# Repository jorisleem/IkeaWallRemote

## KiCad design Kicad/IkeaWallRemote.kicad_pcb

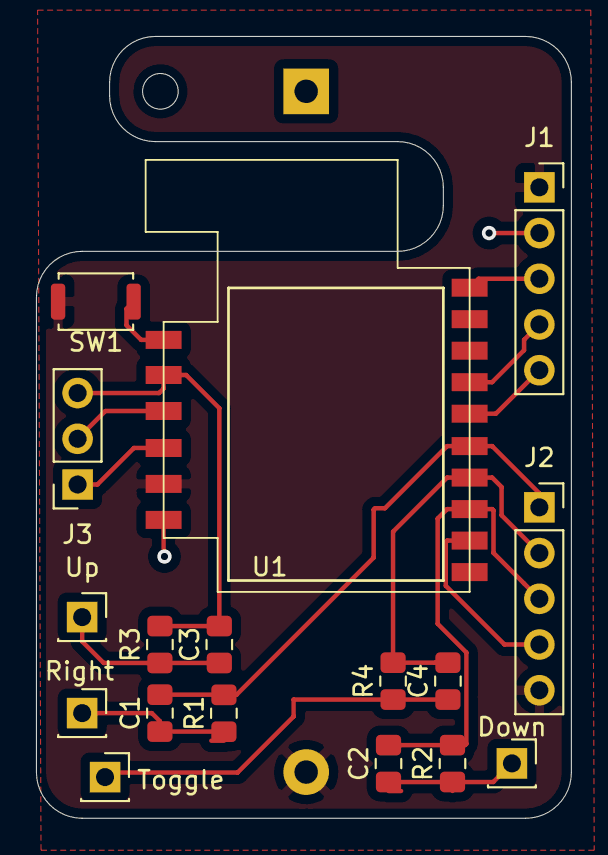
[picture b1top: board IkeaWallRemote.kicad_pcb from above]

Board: 2 copper layers, 29.7 x 43.4 mm, 18 parts (1 on the bottom side), 17 nets.

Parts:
BT1: Battery_Cell; CR123a
C1, C2, C3, C4: 10nf; C_0805_2012Metric_Pad1.15x1.40mm_HandSolder
Down: Conn_01x01_Male; PinSocket_1x01_P2.54mm_Vertical
J1, J2: Conn_01x05_Male; PinSocket_1x05_P2.54mm_Vertical
J3: Conn_01x03_Male; PinSocket_1x03_P2.54mm_Vertical
R1, R2, R3, R4: 487; R_0805_2012Metric_Pad1.15x1.40mm_HandSolder
Right: Conn_01x01_Male; PinSocket_1x01_P2.54mm_Vertical
SW1: SW_Push; SW_Push_SPST_NO_Alps_SKRK
Toggle: Conn_01x01_Male; PinSocket_1x01_P2.54mm_Vertical
U1: TRADFRI; TRADFRI_PCB2.0
Up: Conn_01x01_Male; PinSocket_1x01_P2.54mm_Vertical

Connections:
+3V0: BT1.1, J1.2, U1.6
GND: BT1.2, J1.1, J2.5, SW1.2, U1.5
LED: J3.1, U1.4
Left: J2.4, U1.8
unnamed: C1.1, R1.1, Right.1
unnamed: C2.1, Down.1, R2.1
unnamed: C3.1, R3.1, Up.1
unnamed: C4.1, R4.1, Toggle.1
Off: J3.2, U1.3
PA0: SW1.1, U1.1
PF0: J1.5, U1.12
PF1: J1.4, U1.13
Reset: J1.3, U1.16
Right: C1.2, J2.1, R1.2, U1.11
Toggle: C4.2, J2.2, R4.2, U1.10
Up: C3.2, J3.3, R3.2, U1.2
down: C2.2, J2.3, R2.2, U1.9

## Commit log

2020-11-21 Firt init
